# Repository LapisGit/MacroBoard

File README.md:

# MacroBoard

## Features:
- 6 Keys
- Customizable config without having to change the firmware (technically)
- USB-C
- Powered by a XIAO-RP2040

## CAD:

My case was made using **AutoDesk Fusion Personal.** I started out with making the bottom of the case, and then the top, and that ended in a faliure. So I went ahead and redesigned the entire board, including the PCB and wound up with this!

## PCB:

My PCB was made in KiCad 9, and I decided to add some personal *flair* to the PCB, aswell as the Hack Club logo for *obvious* reasons.

***Here's the model with some of the parts placed in too!***

## Firmware:
I haven't worked on the firmware, pretty much at all, just because I would have zero way to test, my current changes are loading the keymapping via a json file, so no laggy IDE's have to be open everytime. I'm hoping to soon make a GUI for changing the json easier.

Once I have my MacroBoard assembled physically, I will continue making the firmware, but for now, it'll stay in it's current state :)

## BOM:
- Seeed XIAO RP2040
- MX-Style switches (6x)
- SK6812 MINI-E LEDs (2x)
- Blank DSA keycaps (6x)
- M3x16mm screws
- M3x5mx4mm heatset inserts

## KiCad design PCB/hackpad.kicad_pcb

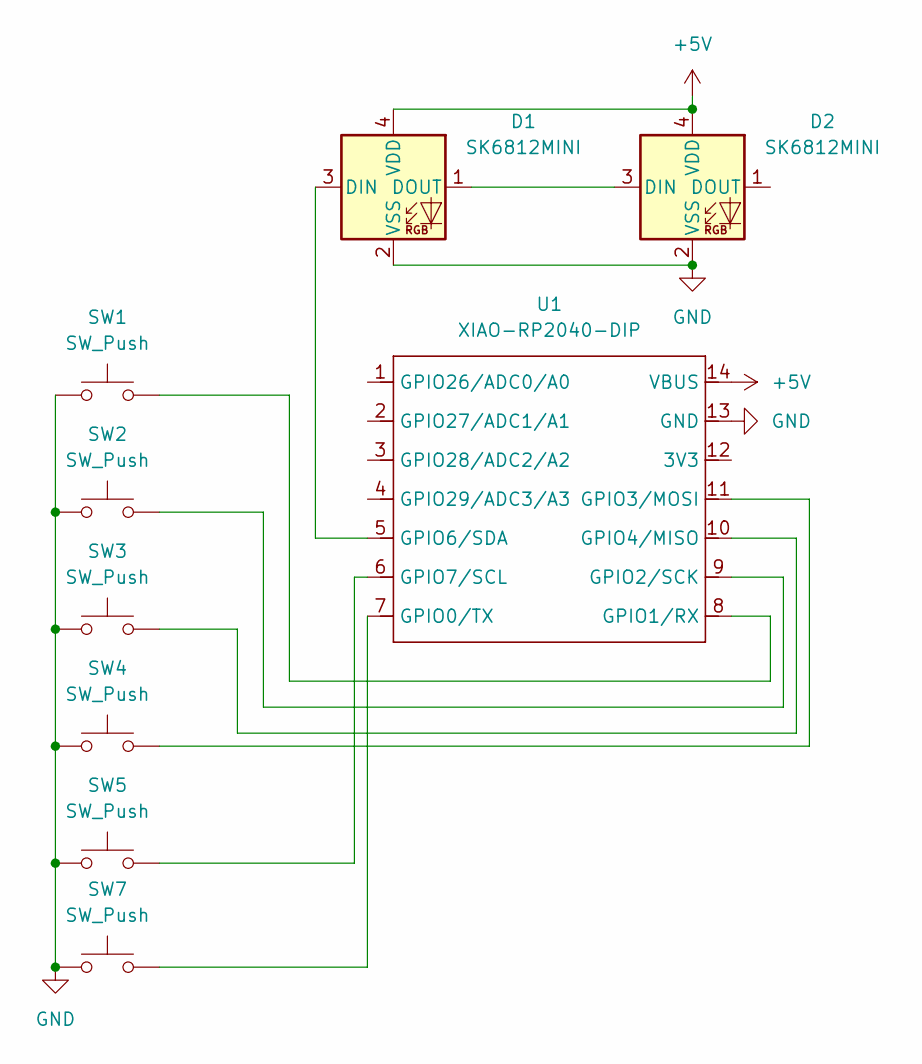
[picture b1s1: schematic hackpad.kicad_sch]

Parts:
D1, D2: SK6812MINI; LED_SK6812MINI_PLCC4_3.5x3.5mm_P1.75mm
SW1, SW2, SW3, SW4, SW5, SW7: SW_Push; SW_Cherry_MX_1.00u_PCB
U1: XIAO-RP2040-DIP

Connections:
+5V: D1.4 (VDD), D2.4 (VDD), U1.14 (VBUS)
GND: D1.2 (VSS), D2.2 (VSS), SW1.1, SW2.1, SW3.1, SW4.1, SW5.1, SW7.1, U1.13 (GND)
unnamed: D1.3 (DIN), U1.5 (GPIO6/SDA)
unnamed: D1.1 (DOUT), D2.3 (DIN)
unnamed: SW7.2, U1.7 (GPIO0/TX)
unnamed: SW1.2, U1.8 (GPIO1/RX)
unnamed: SW2.2, U1.9 (GPIO2/SCK)
unnamed: SW4.2, U1.11 (GPIO3/MOSI)
unnamed: SW3.2, U1.10 (GPIO4/MISO)
unnamed: SW5.2, U1.6 (GPIO7/SCL)

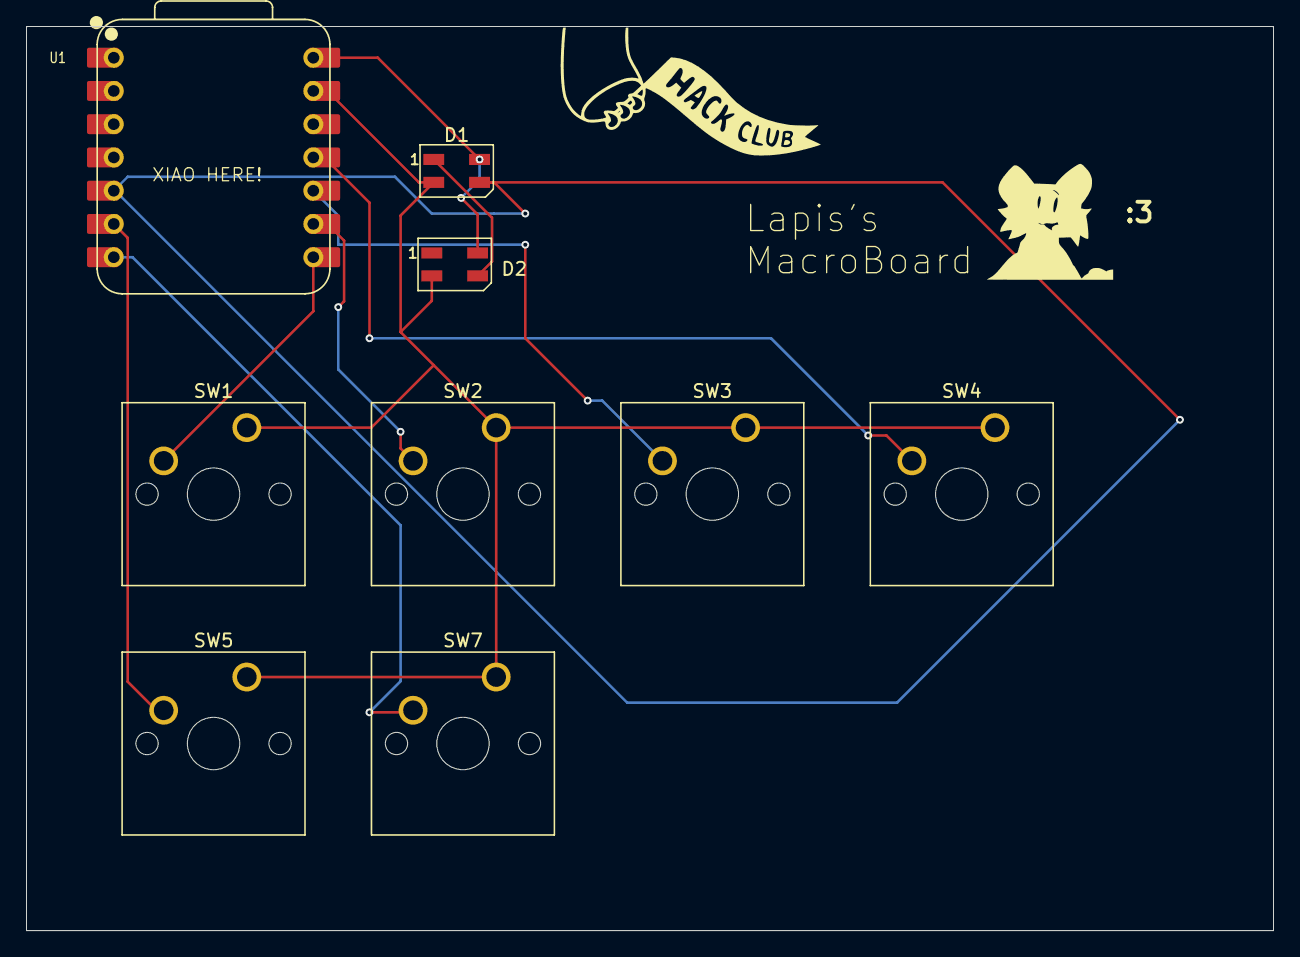
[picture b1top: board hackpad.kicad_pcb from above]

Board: 2 copper layers, 95.2 x 69.1 mm, 11 parts (0 on the bottom side), 10 nets.

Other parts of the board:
:3: LOGO
_: LOGO

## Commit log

2025-06-26 add CAD + PCB files
2025-06-27 add firmware
2025-06-27 get ready for prod
2025-06-27 add BOM
2025-06-27 add firmware section, finish prod
2025-06-27 fix formatting
2025-06-27 fix for product guidelines
2025-06-27 push updated pcb and cad
2025-06-28 update pcb + schematic to not short the entire board (...oops)
    readme update soon
2025-06-28 remove assets folder (its never used)
2025-06-28 update pcb images
